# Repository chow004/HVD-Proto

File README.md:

# HVD-Proto
HDMI Video Divider device prototype development. Copryright DigiPen Institute of Technology.

Project development for the HVD began September, 2014. The project is considered course work for ECE310L and ECE460L.
All submission should be organized into the following sections:

Documents - This section will contain technical documentation, presentation materials, and references used during development.

Hardware - This section contains files related to hardware development mainly including eagle files.

Software - This section sontains files related to software development mainly including code files.

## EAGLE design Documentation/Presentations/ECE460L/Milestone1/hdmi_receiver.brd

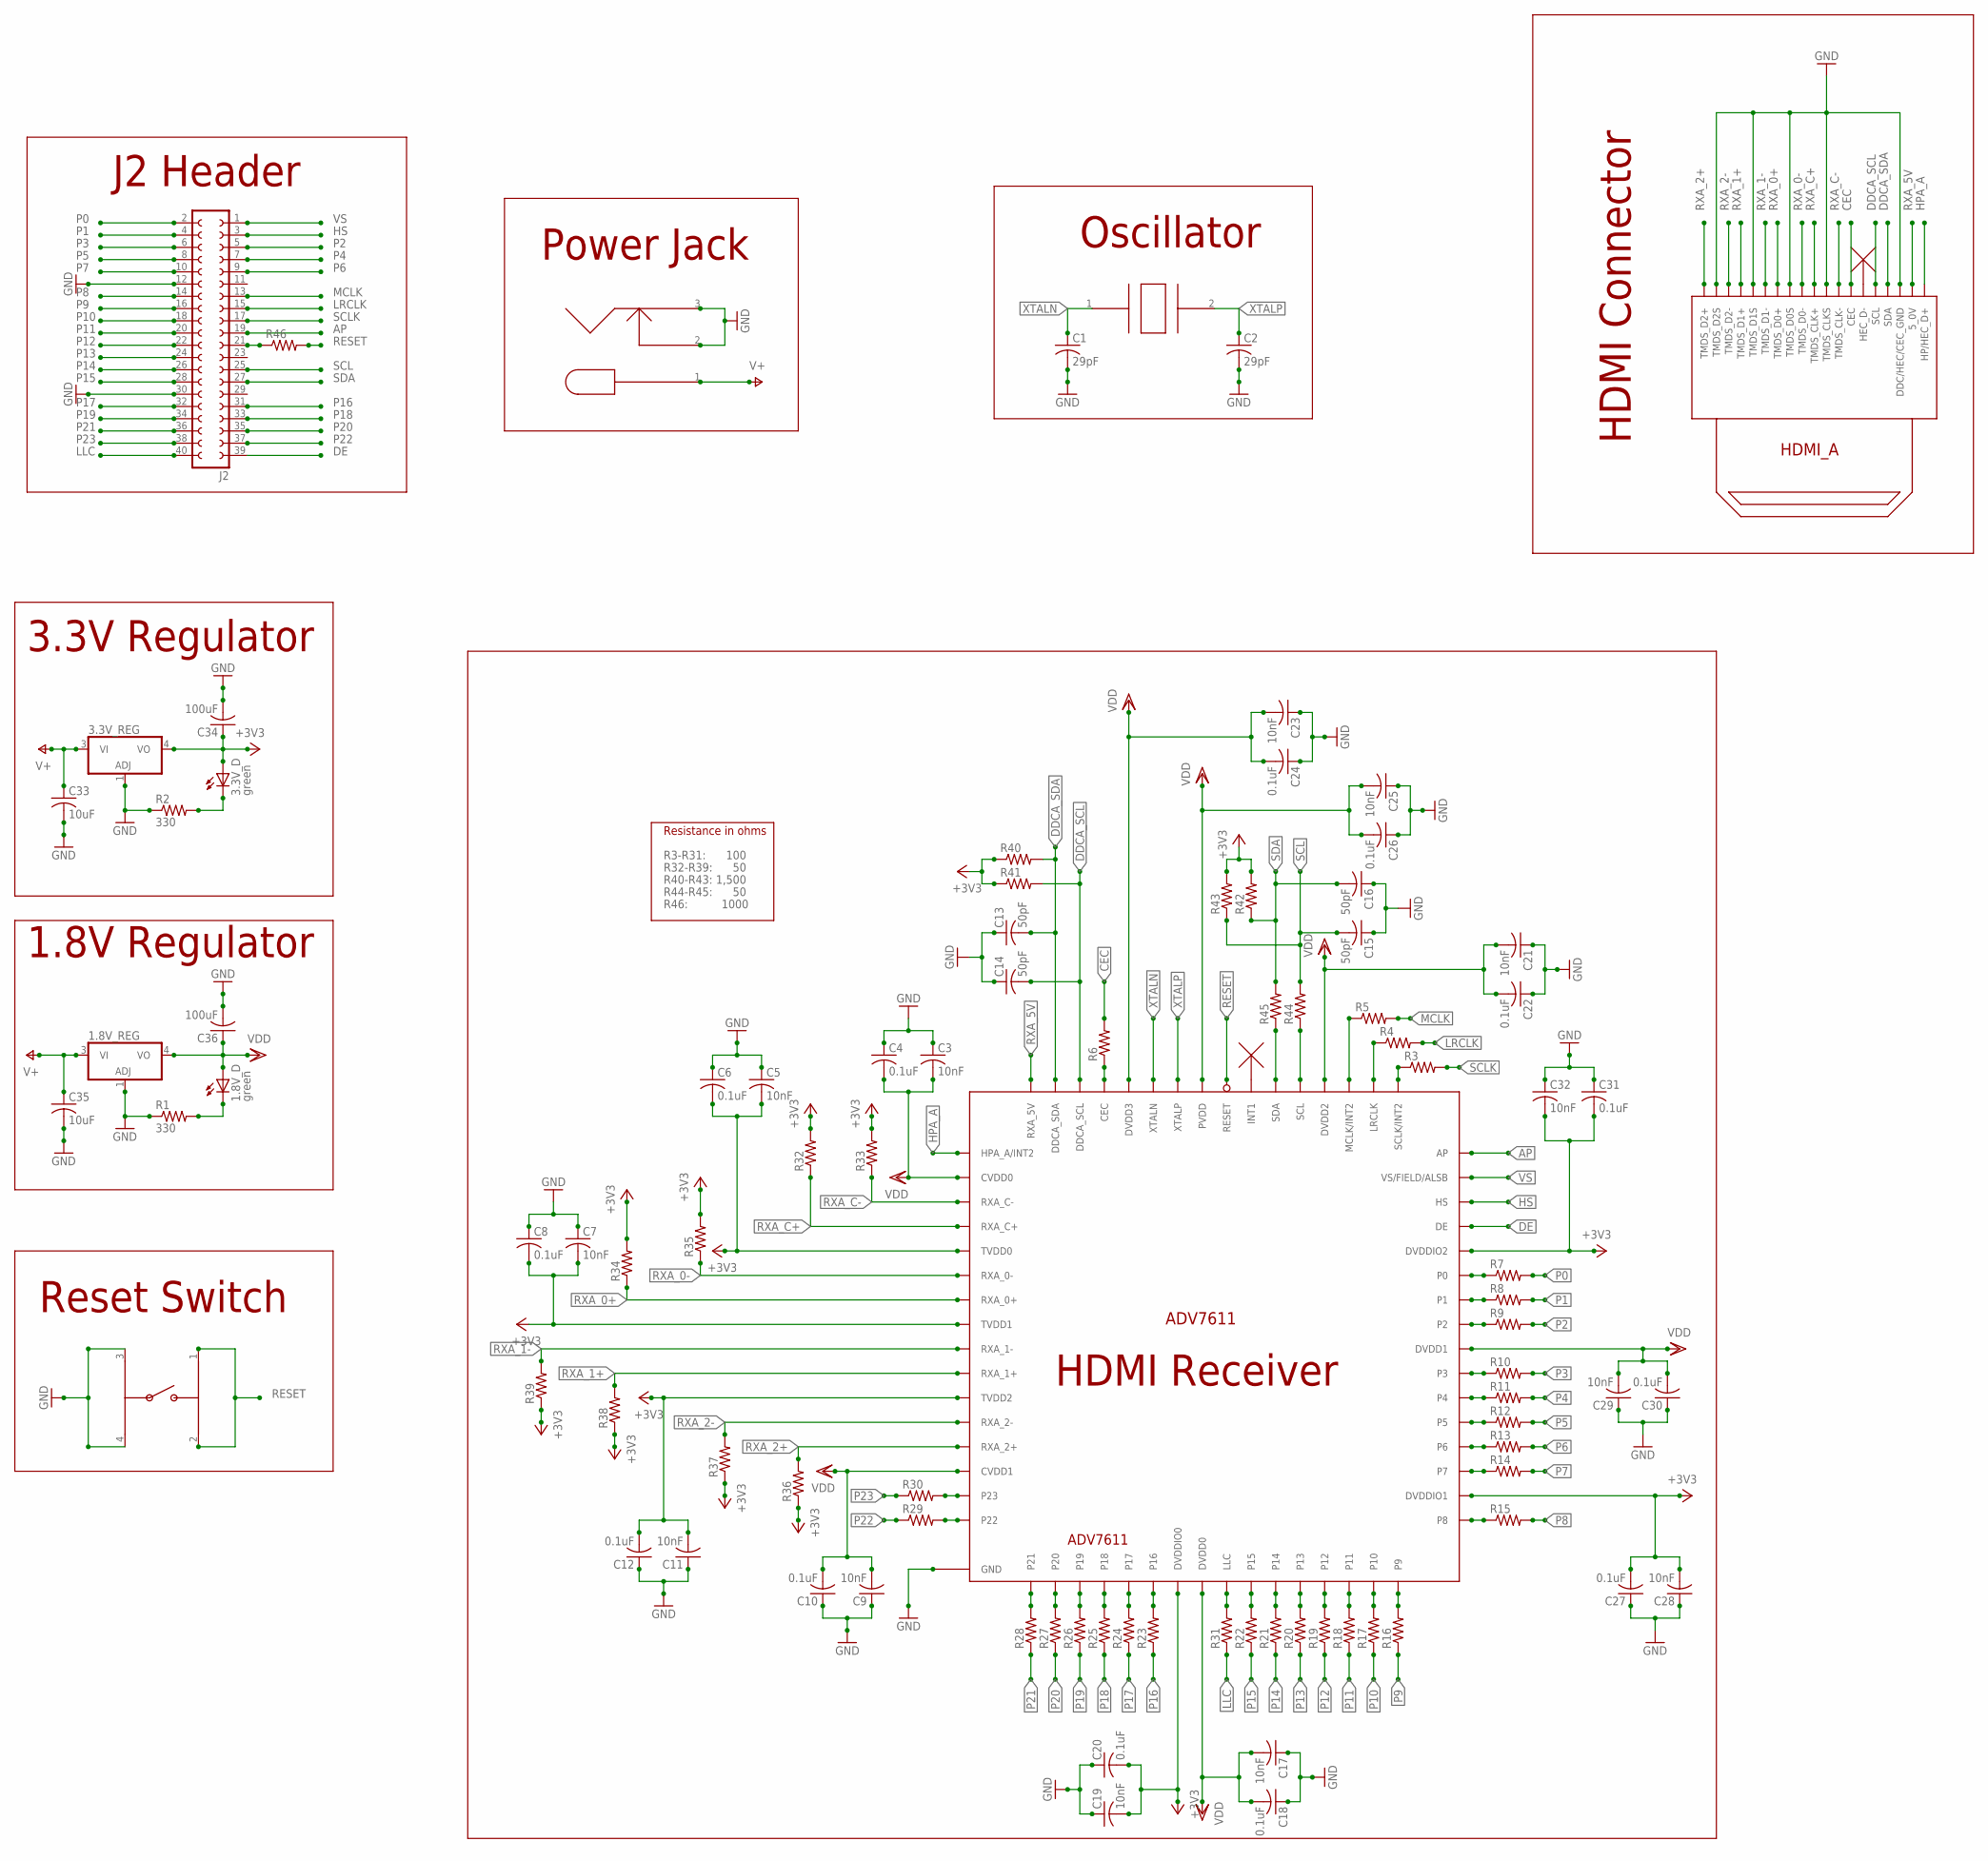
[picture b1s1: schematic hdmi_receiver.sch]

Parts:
1.8V_D, 3.3V_D: green; LED5MM
1.8V_REG, 3.3V_REG: 317EMP; SOT223
ADV7611: ADV7611; LQFP-ST-64-2
C1, C2: 29pF; C1210
C3, C5, C7, C9, C11, C17, C19, C21, C23, C25, C28, C29, C32: 10nF; C0603
C4, C6, C8, C10, C12, C18, C20, C22, C24, C26, C27, C30, C31: 0.1uF; C0603
C13, C14, C15, C16: 50pF; C0603
C33, C35: 10uF; C0603
C34, C36: 100uF; C1206
J2: FE20-2
R1, R2: 330; R0603
R3, R4, R5, R6, R7, R8, R9, R10, R11, R12, R13, R14, R15, R16, R17, R18, R19, R20, R21, R22, R23, R24, R25, R26, R27, R28, R29, R30, R31, R32, R33, R34, R35, R36, R37, R38, R39, R40, R41, R42, R43, R44, R45, R46: R-US_R0603; R0603
U$1: 111RLF
U$2: CRYSTAL_OSC
U$3: CK_SWITCH
U$4: DC_BARREL_CONN

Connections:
+3V3: 3.3V_D.A, 3.3V_REG.4 (VO), ADV7611.5 (TVDD0), ADV7611.8 (TVDD1), ADV7611.11 (TVDD2), ADV7611.23 (DVDDIO0), ADV7611.34 (DVDDIO1), ADV7611.44 (DVDDIO2), C5.2, C6.2, C7.2, C8.2, C11.2, C12.2, C19.2, C20.2, C27.2, C28.2, C31.2, C32.2, C34.1, R32.2, R33.2, R34.2, R35.2, R36.1, R37.1, R38.1, R39.1, R40.1, R41.1, R42.2, R43.2
AP: ADV7611.48 (AP), J2.19
CEC: R6.2, U$1.13 (CEC)
DDCA_SCL: ADV7611.62 (DDCA_SCL), C14.2, R41.2, U$1.15 (SCL)
DDCA_SDA: ADV7611.63 (DDCA_SDA), C13.2, R40.2, U$1.16 (SDA)
DE: ADV7611.45 (DE), J2.39
GND: 1.8V_REG.1 (ADJ), 3.3V_REG.1 (ADJ), ADV7611.0 (GND), C1.2, C2.2, C3.1, C4.1, C5.1, C6.1, C7.1, C8.1, C9.1, C10.1, C11.1, C12.1, C13.1, C14.1, C15.1, C16.1, C17.1, C18.1, C19.1, C20.1, C21.1, C22.1, C23.1, C24.1, C25.1, C26.1, C27.1, C28.1, C29.1, C30.1, C31.1, C32.1, C33.2, C34.2, C35.2, C36.2, J2.12, J2.30, R1.1, R2.1, U$1.2 (TMDS_D2S), U$1.5 (TMDS_D1S), U$1.8 (TMDS_D0S), U$1.11 (TMDS_CLKS), U$1.17 (DDC/HEC/CEC_GND), U$3.3, U$3.4, U$4.2, U$4.3
HPA_A: ADV7611.1 (HPA_A/INT2), U$1.19 (HP/HEC_D+)
HS: ADV7611.46 (HS), J2.3
LLC: J2.40, R31.1
LRCLK: J2.15, R4.2
MCLK: J2.13, R5.2
unnamed: ADV7611.25 (LLC), R31.2
unnamed: 1.8V_D.K (C), R1.2
unnamed: 3.3V_D.K (C), R2.2
unnamed: ADV7611.49 (SCLK/INT2), R3.1
unnamed: ADV7611.50 (LRCLK), R4.1
unnamed: ADV7611.51 (MCLK/INT2), R5.1
unnamed: ADV7611.61 (CEC), R6.1
unnamed: ADV7611.39 (P3), R10.1
unnamed: ADV7611.38 (P4), R11.1
unnamed: ADV7611.37 (P5), R12.1
unnamed: ADV7611.36 (P6), R13.1
unnamed: ADV7611.35 (P7), R14.1
unnamed: ADV7611.54 (SDA), R45.1
unnamed: ADV7611.53 (SCL), R44.1
unnamed: J2.21, R46.1
unnamed: ADV7611.32 (P9), R16.2
unnamed: ADV7611.31 (P10), R17.2
unnamed: ADV7611.30 (P11), R18.2
unnamed: ADV7611.29 (P12), R19.2
unnamed: ADV7611.28 (P13), R20.2
unnamed: ADV7611.27 (P14), R21.2
unnamed: ADV7611.26 (P15), R22.2
unnamed: ADV7611.22 (P16), R23.2
unnamed: ADV7611.21 (P17), R24.2
unnamed: ADV7611.20 (P18), R25.2
unnamed: ADV7611.19, R26.2
unnamed: ADV7611.18 (P20), R27.2
unnamed: ADV7611.17 (P21), R28.2
unnamed: ADV7611.16 (P22), R29.2
unnamed: ADV7611.15 (P23), R30.2
unnamed: ADV7611.33 (P8), R15.1
unnamed: ADV7611.41 (P2), R9.1
unnamed: ADV7611.42 (P1), R8.1
unnamed: ADV7611.43 (P0), R7.1
P0: J2.2, R7.2
P1: J2.4, R8.2
P2: J2.5, R9.2
P3: J2.6, R10.2
P4: J2.7, R11.2
P5: J2.8, R12.2
P6: J2.9, R13.2
P7: J2.10, R14.2
P8: J2.14, R15.2
P9: J2.16, R16.1
P10: J2.18, R17.1
P11: J2.20, R18.1
P12: J2.22, R19.1
P13: J2.24, R20.1
P14: J2.26, R21.1
P15: J2.28, R22.1
P16: J2.31, R23.1
P17: J2.32, R24.1
P18: J2.33, R25.1
P19: J2.34, R26.1
P20: J2.35, R27.1
P21: J2.36, R28.1
P22: J2.37, R29.1
P23: J2.38, R30.1
RESET: ADV7611.56 (RESET), R46.2, U$3.1, U$3.2
RXA_0+: ADV7611.7 (RXA_0+), R34.1, U$1.7 (TMDS_D0+)
RXA_0-: ADV7611.6 (RXA_0-), R35.1, U$1.9 (TMDS_D0-)
RXA_1+: ADV7611.10 (RXA_1+), R38.2, U$1.4 (TMDS_D1+)
RXA_1-: ADV7611.9 (RXA_1-), R39.2, U$1.6 (TMDS_D1-)
RXA_2+: ADV7611.13 (RXA_2+), R36.2, U$1.1 (TMDS_D2+)
RXA_2-: ADV7611.12 (RXA_2-), R37.2, U$1.3 (TMDS_D2-)
RXA_5V: ADV7611.64 (RXA_5V), U$1.18 (5_0V)
RXA_C+: ADV7611.4 (RXA_C+), R32.1, U$1.10 (TMDS_CLK+)
RXA_C-: ADV7611.3 (RXA_C-), R33.1, U$1.12 (TMDS_CLK-)
SCL: C15.2, J2.25, R43.1, R44.2
SCLK: J2.17, R3.2
SDA: C16.2, J2.27, R42.1, R45.2
V+: 1.8V_REG.3 (VI), 3.3V_REG.3 (VI), C33.1, C35.1, U$4.1
VDD: 1.8V_D.A, 1.8V_REG.4 (VO), ADV7611.2 (CVDD0), ADV7611.14 (CVDD1), ADV7611.24 (DVDD0), ADV7611.40 (DVDD1), ADV7611.52 (DVDD2), ADV7611.57 (PVDD), ADV7611.60 (DVDD3), C3.2, C4.2, C9.2, C10.2, C17.2, C18.2, C21.2, C22.2, C23.2, C24.2, C25.2, C26.2, C29.2, C30.2, C36.1
VS: ADV7611.47 (VS/FIELD/ALSB), J2.1
XTALN: ADV7611.59 (XTALN), C1.1, U$2.1
XTALP: ADV7611.58 (XTALP), C2.1, U$2.2

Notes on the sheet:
R3-R31: 100
Resistance in ohms
R32-R39: 50
R40-R43: 1,500
R44-R45: 50
R46: 1000
RESET
HDMI Receiver
J2 Header
Power Jack
Oscillator
HDMI Connector
3.3V Regulator
1.8V Regulator
Reset Switch
ADV7611

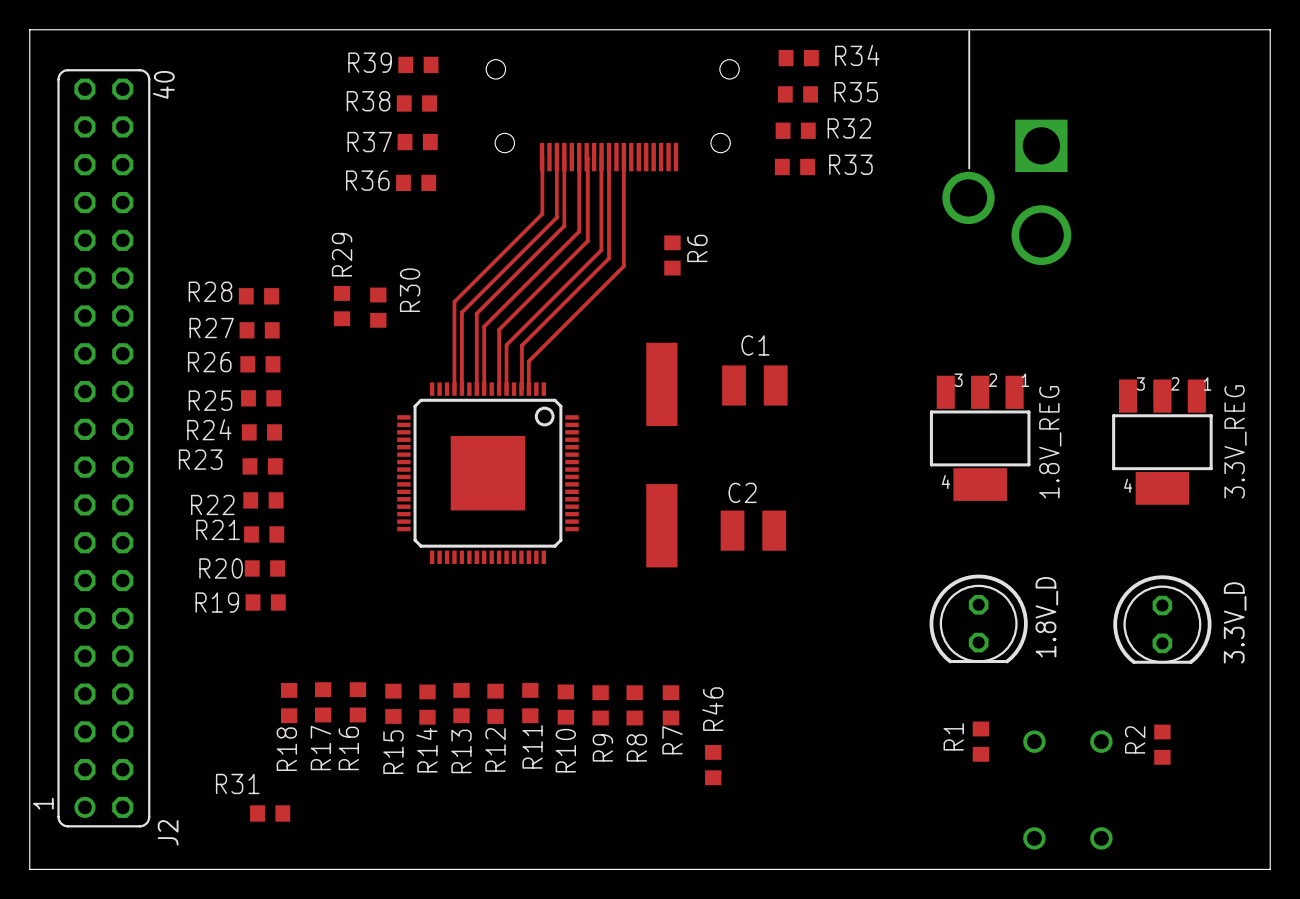
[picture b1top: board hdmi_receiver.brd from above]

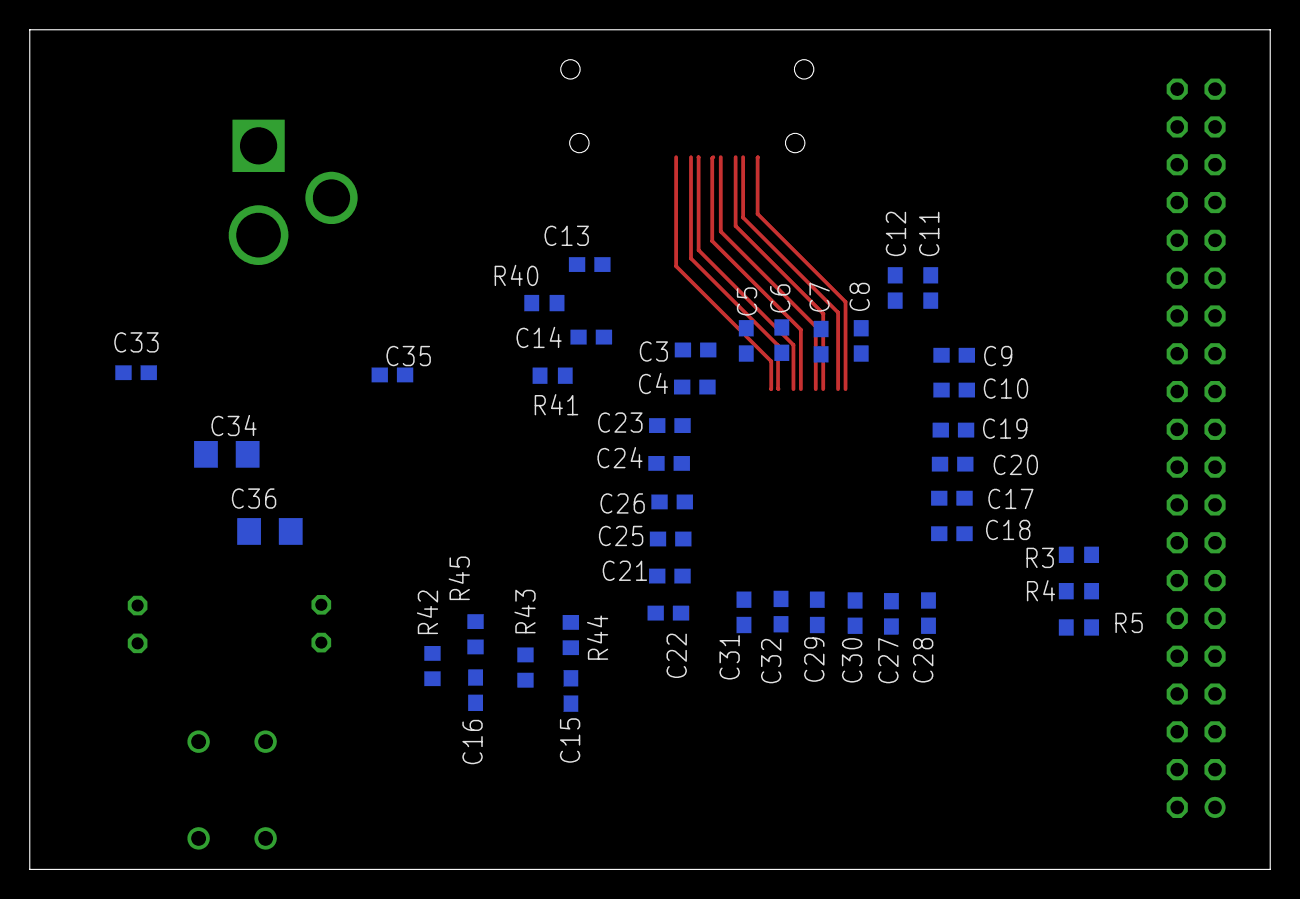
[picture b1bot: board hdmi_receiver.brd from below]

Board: 2 copper layers, 83.3 x 56.4 mm, 92 parts (43 on the bottom side), 88 nets.

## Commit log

2015-01-29 Initial Commit
    Adding all types of project files from DigiPen workspace
2015-02-12 First Code Commit
    Fixed I²C bugs. Implemented simple interface for I²C operations using
    the buttons, switches, hex displays, and leds.
2015-02-12 Update .gitignore
    Removed ignore for .jpg in order to include project diagrams and image files.
2015-02-12 Simulation Testbench files
    + image of timeline edits
2015-03-17 Main Program Updates
    Updating main always to integrate push button actions:
    (0) Write single byte with input value to input address
    (1) Read single byte value at input address
    (2) Write 5 bytes of data for configuring HDMI to VGA
    Added code to ensure transmit register was shifted correctly between
    bytes during a single write. Fixed problem with I2C failing when
2015-03-26 ADV7611 Initialization
    - Inferred M9K memory
    - Changed method of interaction for read/write operations to support
    multiple slave devices
    - Included HDMI receiver initialization code using inferred memory and
    .mif file.
2015-03-26 Initialization Update & EDID memory
    - Update HDMI_Receive.v for more robust initialization
    - Update adv7611.mif with more initialization writes
    as well as EDID data writes
    - Update ram_init.v to support increased memory and address size.
2015-04-13 Testbench update
    Updated ModelSim files and I2C module in order to test bug fixes the I2C
    protocol. Fixes need to be tested on platform.
2015-04-13 Main Program Update
    Attempting to fix I²C and I did fix a bug but still having some issues.
2015-04-16 I2C update
    Changed I2C structure in order to prevent a state deadlock. It was
    getting stuck in read/write state with certain conditions. Particularly
    under risk if the chip NACKed
2015-04-24 Main Logic Update
    This build has a highest I²C transfer success rate. As a result the EDID
    and configuration can be completed so that the PC detects the ADV7611 as
    an HDMI sink. However the ADV7611 still does not produce LLC output or
    lock onto all sync signals.

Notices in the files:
Documentation/Presentations/ECE460L/Milestone1/hdmi_receiver.brd:
Copyright DigiPen Inst. of Technology
